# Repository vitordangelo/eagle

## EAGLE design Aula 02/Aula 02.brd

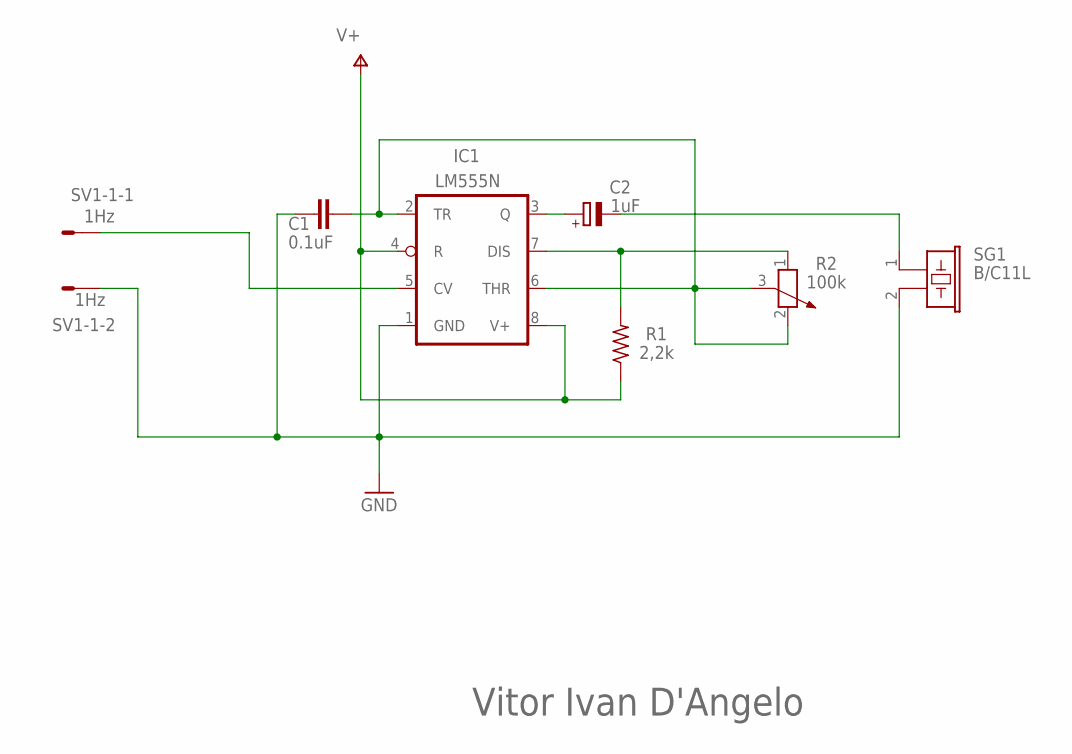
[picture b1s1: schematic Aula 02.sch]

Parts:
C1: 0.1uF; C025-040X050
C2: 1uF; E2-5
IC1: LM555N; DIL08
R1: 2,2k; 0204/7
R2: 100k; PT-10
SG1: B/C11L
SV1-1: 1Hz; L02P

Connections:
GND: C1.1, IC1.1 (GND), SG1.2, SV1-1.2
unnamed: C1.2, IC1.2 (TR), IC1.6 (THR), R2.2, R2.3
unnamed: C2.+, IC1.3 (Q)
unnamed: IC1.5 (CV), SV1-1.1
unnamed: C2.-, SG1.1
unnamed: IC1.7 (DIS), R1.2, R2.1
V+: IC1.4 (R), IC1.8 (V+), R1.1

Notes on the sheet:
Vitor Ivan D'Angelo

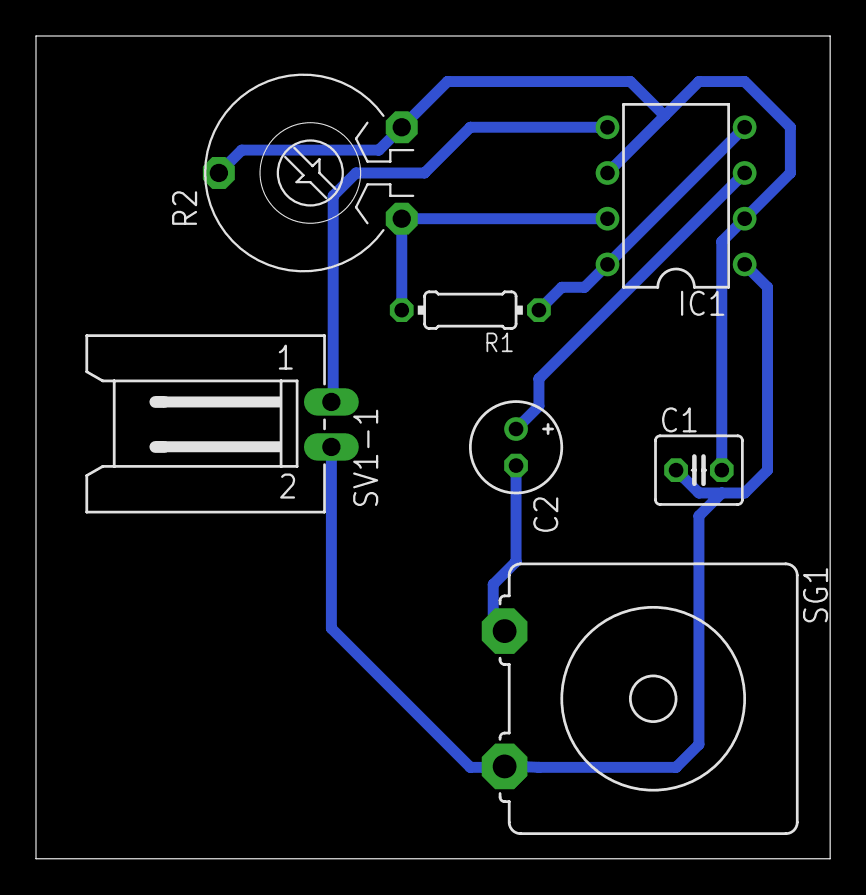
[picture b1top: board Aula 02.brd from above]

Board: 2 copper layers, 44.1 x 45.7 mm, 7 parts (0 on the bottom side), 7 nets.
